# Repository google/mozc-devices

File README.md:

Circuit diagrams and firmware source code for Gboard DIY keyboards, previously
known as Google Japanese Input / Gboard April Fools.

This is not an officially supported Google product.

# Products

Please refer to the README in each directory for more details.

<table>
<tr>
<td>

[Google 日本語入力 ドラムセットバージョン](https://archive.google/drumsetkeyboard/)<br>
[Google Japanese Input Drum set version](https://archive.google/drumsetkeyboard/)

変換の煩わしさを感じさせない思いどおりの日本語入力を提供します。

- [Announce](https://blog.google/intl/ja-jp/products/android-chrome-play/2010_04_google/)
- Release date: Apr 1, 2010
- Source: Not open source

</td>
<td>

[Google 日本語入力 モールスバージョン](http://www.google.co.jp/ime/-.-.html)<br>
[Google Japanese Input Morse version](http://www.google.co.jp/ime/-.-.html)

モールス符号で思いどおりの日本語入力

- [Promotional video](https://www.youtube.com/watch?v=u5AYb778pwA)
- [Announce](https://japan.googleblog.com/2012/04/google.html)
- [Technical details](http://googledevjp.blogspot.jp/2012/06/google.html)
- Release date: Apr 1, 2012
- Source: [/third_party/mozc-morse](./third_party/mozc-morse)

</td>
</tr>
<tr>
<td>

[Google 日本語入力 パタパタバージョン](http://www.google.co.jp/ime/patapata/)<br>
[Google Japanese Input Patapata version](http://www.google.co.jp/ime/patapata/)

もう、なにも覚える必要はありません。
押して離すだけの日本語入力。

- [Promotional video](https://www.youtube.com/watch?v=HzUDAaYMNsA)
- [Announce](https://japan.googleblog.com/2013/04/google-patapata.html)
- [Technical details](http://googledevjp.blogspot.jp/2013/10/google.html)
- Release date: Apr 1, 2013
- Source: [/third_party/mozc-flap](./third_party/mozc-flap)

</td>
<td>

[Google 日本語入力 マジックハンドバージョン](https://archive.google/ime/m9/)<br>
[Google Japanese Input Magic hand version](https://archive.google/ime/m9/)

マジックハンドでらくらく入力

- [Promotional video](https://www.youtube.com/watch?v=0u1zoaJYAmw)
- [Announce](https://blog.google/intl/ja-jp/products/android-chrome-play/2014_04_m9/)
- Release date: Apr 1, 2014
- Source: Not open source

</td>
</tr>
<tr>
<td>

[Google 日本語入力 ピロピロバージョン](https://www.google.co.jp/ime/___o/)<br>
[Google Japanese Input Piropiro version](https://www.google.co.jp/ime/___o/)

もうキーはいらない

- [Promotional video](https://www.youtube.com/watch?v=gAgOnQqyDz0)
- [Announce](https://japan.googleblog.com/2015/04/piropiro.html)
- Release date: Apr 1, 2015
- Source: [/mozc-piropiro](./mozc-piropiro)

</td>
<td>

[Google 日本語入力 物理フリックバージョン](https://www.google.co.jp/ime/furikku/)<br>
[Google Japanese Input Physical Flick version](https://www.google.co.jp/ime/furikku/)

さわれるフリック

- [Promotional video](https://www.youtube.com/watch?v=5LI1PysAlkU)
- [Announce](https://japan.googleblog.com/2016/04/furikku.html)
- Release date: Apr 1, 2016
- Source: [/mozc-furikku](./mozc-furikku)

</td>
</tr>
<tr>
<td>

[日本語入力 プチプチバージョン](https://landing.google.co.jp/ime/ooooo/)<br>
[Google Japanese Input Puchi Puchi version](https://landing.google.co.jp/ime/ooooo/)

空気のように、軽やかな入力。

- [Promotional video](https://www.youtube.com/watch?v=RkJZDvHMyTA)
- [Announce](https://japan.googleblog.com/2017/04/ooooo.html)
- Release date: Apr 1, 2017
- Source: [/third_party/mozc-puchi](./third_party/mozc-puchi)

</td>
<td>

[Gboard 物理手書きバージョン](https://landing.google.co.jp/tegaki/)<br>
[Gboard Physical Handwriting version](https://landing.google.co.jp/tegaki/)

新しいタイプの手書き入力。

- [Promotional video](https://www.youtube.com/watch?v=guJnFY1R4I0)
- [Announce](https://japan.googleblog.com/2018/04/tegaki.html)
- [Technical details](https://developers-jp.googleblog.com/2018/04/tegaki.html)
- Release date: Apr 1, 2018
- Source: [/mozc-nazoru](./mozc-nazoru)

</td>
</tr>
<tr>
<td>

[Gboard スプーン曲げバージョン](https://landing.google.co.jp/---o/)<br>
[Gboard Spoon Bending version](https://landing.google.co.jp/---o/)

タネも仕掛けもない、柔軟な入力。

- [Promotional video](https://www.youtube.com/watch?v=DeJY5d14qKs)
- [Announce](https://japan.googleblog.com/2019/04/mageru.html)
- Release date: Apr 1, 2019
- Source:
  - [/mozc-mageru](./mozc-mageru) for firmware, schematics, and PCB layout.
  - [/third_party/mozc-mageru](./third_party/mozc-mageru) for 3D model.

</td>
<td>

[Gboard 湯呑みバージョン](https://g.co/yunomi/)<br>
[Gboard yunomi version](https://g.co/yunomi/)

もう、おすしかない。

- [Promotional video](https://www.youtube.com/watch?v=20pC05yisRM)
- [Announce](https://japan.googleblog.com/2021/10/gboard.html)
- Release date: Oct 1, 2021
- Source: [/mozc-yunomi](./mozc-yunomi)

</td>
</tr>
<tr>
<td>

[Gboard 棒バージョン](https://g.co/____)<br>
[Gboard bar version](https://g.co/____)

キーの次はボーです。

- [Promotional video](https://www.youtube.com/watch?v=9G3DWHf1xX0)
- [Announce](https://japan.googleblog.com/2022/10/gboard-2022.html)
- Release date: Oct 1, 2022
- Source: [/mozc-bar](./mozc-bar)

</td>
<td>

[Gboard 帽バージョン](https://g.co/CAPS)<br>
[Gboard CAPS version](https://g.co/CAPS)

入力は、帽険だ。

- [Promotional video](https://www.youtube.com/watch?v=6vib77CUxNM)
- [Announce](https://japan.googleblog.com/2023/10/caps.html)
- Release date: Oct 1, 2023
- Source: [/mozc-caps](./mozc-caps)

</td>
</tr>
<tr>
<td>

[Gboard 両面バージョン](https://g.co/double-sided)<br>
[Gboard double sided version](https://g.co/double-sided)

表面かと思ったら裏面でした。

- [Promotional video](https://www.youtube.com/watch?v=EHqPrHTN1dU)
- [Announce](https://blog.google/intl/ja-jp/products/android-chrome-play/gboard-2024)
- Release date: Oct 1, 2024
- Source: [/mozc-doublesided](./mozc-doublesided)

</td>
<td>

[Gboard ダイヤルバージョン](./mozc-dial/README_ja.md)<br>
[Gboard Dial Version](./mozc-dial)

まるくおさめました。

- [Promotional video](https://youtu.be/BgdWyD0cBx4)
- [Announce](https://blog.google/intl/ja-jp/products/android-chrome-play/gboard-2025)
- Release date: Oct 1, 2025
- Source: [/mozc-dial](./mozc-dial)

</td>
</tr>
<tr>
<td>

[Gboard くるくる バージョン](./mozc-conveyorbelt/README_ja.md)<br>
[Gboard Conveyor Belt version](./mozc-conveyorbelt)

流れるような文字入力を

- [Promotional video](https://www.youtube.com/watch?v=DAn34l_YrUM)
- [Announce](https://blog.google/intl/ja-jp/products/android-chrome-play/gboard-2026/)
- Release date: Oct 1, 2026
- Source: [/mozc-conveyorbelt](./mozc-conveyorbelt)

</td>
<td>
</td>
</tr>
</table>

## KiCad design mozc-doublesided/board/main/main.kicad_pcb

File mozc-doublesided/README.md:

# Gboard double sided version

This directory contains the firmware and hardware design for Gboard double sided
version, which was released on **Oct 1, 2024**.

This is not an officially supported Google product.

## Contents

The directory structure is as follows:

-   case/ : STL files for case
-   board/ : KiCad schematics and PCB layouts
-   firmware/ : Firmware resources for STM32CubeIDE
-   gerber/ : Gerber data for PCB production and assembly

## Building Gboard double-sided Version

### Parts

-   Assembled A Type Board: 26 boards (incl. 1 primary board) - See BOM below
-   Assembled B Type Board: 26 boards (incl. 1 primary board) - See BOM below
-   USB Board: 1 board - See BOM below
-   Cable A; JST ZH 1.5mm pitch 8pin 100mm forward double head: 25 units
-   Cable B; JST ZH 1.5mm pitch 7pin 100mm forward double head: 1 units
-   Pin Header; 1x4 pin 2.54mm pitch 12+mm height,
    ([sample](https://akizukidenshi.com/catalog/g/g101382/)): 52 headers.
-   3D printed case: 26 pcs
-   Self tapping screw (M2 10mm): 52 pcs
-   Key switch (Cherry MX or compatible): 208 pcs.
-   Key caps (For Cherry MX switch): 208 pcs.

#### A Type Board BOM

| Reference | Description                         | Qty | Note               |
| --------- | ----------------------------------- | --- | ------------------ |
| R1-R2     | 0402(metric: 1005) Resistor 510 ohm | 2   |                    |
| R3-R4     | 0603(metric: 1608) Resistor 1K ohm  | 2   | Primary board only |
| J2-J3     | JST S8B-ZR                          | 2   |                    |
| J4        | JST S7B-ZR                          | 1   | Primary board only |
| U1        | STMicro STM32F042F4P6               | 1   |                    |
| SW1-SW4   | Kailh CPG151101S11-1                | 4   |                    |
| D1-D4     | OPSCO Optoelectronics SK6812MINI-E  | 4   |                    |
| D5-D8     | 0805(metric: 2012) Small Signal Switching Diode | 4   |        |
| C1        | 0402(metric: 1005) Capacitor 0.1uF  | 1   |                    |

The parts that are only on the primary board are not included in the BOM file
(in `gerber/` directory), so make sure that you choose one board to be the
primary board and solder in the primary board specific parts.

#### B Type Board BOM

Reference | Description                                     | Qty | Note
--------- | ----------------------------------------------- | --- | ----
R2        | 0402(metric: 1005) Resistor 510 ohm             | 1   |
SW1-SW4   | Kailh CPG151101S11-1                            | 4   |
D1-D4     | OPSCO Optoelectronics SK6812MINI-E              | 4   |
D5-D8     | 0805(metric: 2012) Small Signal Switching Diode | 4   |

#### USB Board BOM

Reference | Description                          | Qty | Note
--------- | ------------------------------------ | --- | ----
U1        | 1A/3.3V Regulator AMS1117-3.3        | 1   |
R1-R2     | 0402(metric: 1005) Resistor 5.1K ohm | 2   |
R3-R4     | 0402(metric: 1005) Resistor 22 ohm   | 2   |
R5        | 0402(metric: 1005) Resistor 1.5K ohm | 1   |
J1        | JST S7B-ZR                           | 1   |
J2        | USB Type-C 16pin connector           | 1   |
C1        | 0402(metric: 1005) Capacitor 10uF    | 1   |
C2        | 0402(metric: 1005) Capacitor 2.2uF   | 1   |
C3-C4     | 0402(metric: 1005) Capacitor 47pF    | 2   |

### Hardware

#### Step 1: Prepare 3d printed parts

The `case/` directory of this repository has STL files for the case. The case
consists of 26 parts (case00.stl - case25.stl). Each part has a number engraved
on the inside. For example, when assembling, you will insert the protrusion of
case 0 into the hole of case 1.

We also provide a jig (`case/jig.stl`) for soldering between the A type boards
and B type boards. Please print this too.

#### Step 2: Prepare PCB

**PCB Production and Assembly**

First, you need to build 26 A type boards and 26 B type boards, and one USB
board. You may be able to use existing gerber data, BOM, and CPL (positions)
from `gerber/` directory.

Board Type | Gerber         | BOM                | CPL
---------- | -------------- | ------------------ | ------------------------
A          | main_panel.zip | main_panel_bom.csv | main_panel_positions.csv
B          | sub_panel.zip  | sub_panel_bom.csv  | sub_panel_positions.csv
USB        | usb.zip        | usb_bom.csv        | usb_positions.csv

Prepared board data for the A type board and the B type board contains 9 boards
in a panel. So, you need to produce 3 panels to build 27 (26 required + 1 spare)
boards. You also need one USB board.

**Firmware upload**

Next, let's burn the prebuilt firmware.

Connect the following 4 pads, SWDIO, SWCLK, GND, and +3.3V with ST-LINK. You can
use
[STM32CubeProgrammer](https://www.st.com/ja/development-tools/stm32cubeprog.html)
to configure the device and to burn the prebuilt firmware. There's no connector,
just holes in the PCB so make sure you keep a secure connection while
programming the device.

Once the programmer establishes the connection with the A type board, you need
to write the `Option bytes`. Under the `User Configuration` section, you will
see the `BOOT_SEL` bit. You need to ensure the bit is unchecked before pushing
the `Apply` button.

Next, you will go to the `Erasing & Programming` section to burn the prebuilt
firmware, `firmware/prebuilt/mozc.elf`. Select the binary from the `Browse`
button, put `0x08000000` for the `Start address`, then press the `Start
Programming` button.

You need to burn the same settings and firmware into all the Boards A.

**Primary A Type Board Specific Modifications**

You need to choose one of the A type boards to be the primary A type board and
add three parts to it.

1.  J4 JST S7B-ZR connector header
2.  R3 0603 Resistor 1K ohm
3.  R4 0603 Resistor 1K ohm

**Construct the A/B Type Board Pair Modules**

You need to prepare 26 pairs of the A type board and B type board. They should
be paired as the following picture shows. Each `P Connector` and each `S
connector` should be connected using the 1x4 pin headers respectively.

Make sure that the `IN` side of the A type board and B type board face each
other.

Also, the distance should be adjusted to fit the case. It will help to print the
included jig STL to hold both boards while soldering the pin headers.

#### Step 3: Insert PCB to case

**Primary A/B Pair Module**

Connect the primary module and the USB board.

Insert the USB board into case 0.

**All Pair Modules**

Insert each paired module into a case. You need to ensure the A type board is
always placed on the bottom side.

#### Step 4: Connect the cases together

You need to connect all the `UP` socket and `DOWN` socket pairs. Please be
careful not to connect the same type of socket, i.e. `UP` and `UP`, or `DOWN`
and `DOWN` together. It will cause a short circuit and destroy the chips when
powered on. If you notice a smell or see smoke, disconnect the power
immediately. This may prevent damage to the boards.

The below picture shows the connections. Please make sure that module 0 and
module 25 are not connected to each other.

Note that this picture is simplified and doesn't reflect the 3d structure of the
keyboard. So, module 25 will be placed upside down.

You can use screws to keep the boards tightly connected.

### Firmware

#### Step 1: Environment setup

You need to install STMicroelectronics's official tools to develop STM32.

-   [STM32CubeIDE](https://www.st.com/en/development-tools/stm32cubeide.html) -
    Confirmed with 1.16.1.
-   [STM32CubeMX](https://www.st.com/en/development-tools/stm32cubemx.html) -
    Confirmed with 6.12.1.

Alternatively, you can use Visual Studio Code with the STM32 VS Code Extension,
STM32CubeMX, and STM32CubeCLT if your development environment is not on Windows.

-   [Visual Studio Code](https://code.visualstudio.com/) - Confirmed with
    1.93.0.
-   [STM32 VS Code Extension](https://marketplace.visualstudio.com/items?itemName=stmicroelectronics.stm32-vscode-extension) -
    Confirmed with 2.1.0.
-   [STM32CubeCLT](https://www.st.com/en/development-tools/stm32cubeclt.html) -
    Confirmed with 1.16.1. You will be asked to specify the path to the VS Code
    Extension. You may add `{ "STM32VSCodeExtension.cubeCLT.path":
    "/opt/ST/STM32CubeCLT_1.16.1" }` to `.vscode/settings.json`.

    You will need the
    [ST-LINK](https://www.st.com/ja/development-tools/st-link-v2.html) or
    something equivalent to upload the firmware.

#### Step 2: Compile and upload

**Steps for the STM32CubeIDE:**

1.  Launch STM32CubeIDE with `mozc-doublesided` directory as `workspace`.
2.  Start a project via `Start new project from STM32CubeMX file (.ioc)` to open
    a configuration dialog.
3.  Select `firmware/mozc-doublesided.ioc` as `STM32CubeMX .ioc file` and push
    `Finish` button to generated required resources.
4.  Apply patches. (See the following instructions)
5.  Set `Release` as the active project, from `Project > Build Configurations >
    Set Active > 2 Release`. `Debug` doesn't fit the available memory size.
6.  Build, from `Project > Build All`.

The built binary will be produced at `firmware/Release/firmware.elf`.

**Steps for the Visual Studio Code:**

1.  Open `firmware/mozc-doublesided.ioc` by STM32CubeMX and push the `GENERATE
    CODE` button. You may need to follow instructions if you are asked to
    install something required in the process.
2.  Launch VSCode and open the folder `firmware`.
3.  Apply patches. (See the following instructions)
4.  Select `Release` or `RelWithDebInfo` from the build presets. `Debug` doesn't
    fit the available memory size.
5.  `Build` from the status bar, or other user interfaces.

The built binary will be produced at `build/Release/firmware.elf`.

If you saw errors on linking the binary involving `STM32F042F6Px_FLASH.ld`, you
may need a patch to make it work with your installed toolchain.

Try `patch < STM32F042F6Px_FLASH.ld.diff`.

**Steps to apply patches:**

In the `firmware` directory, apply the `firmware.diff` patch to the generate
resources via the following command.

`$ patch -p1 < firmware.diff`

## License

See [LICENSE](../LICENSE) file in this directory.

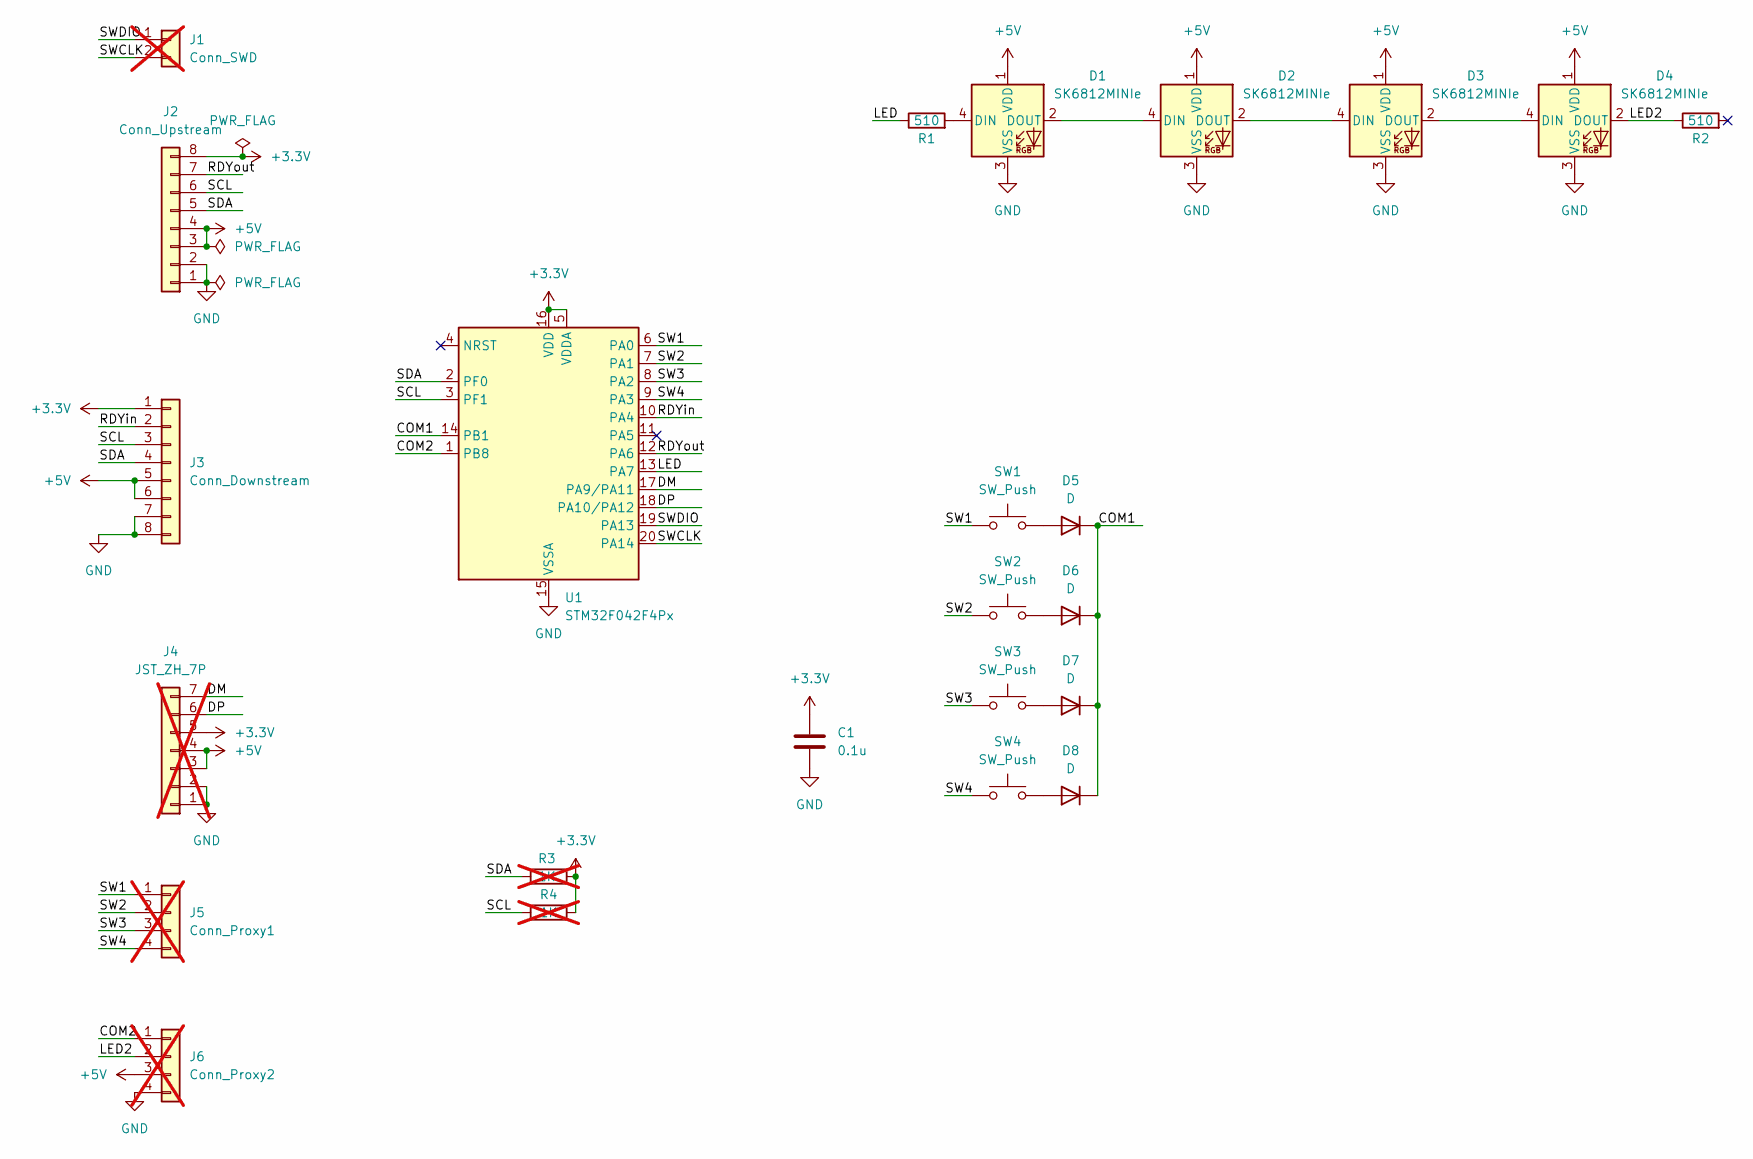
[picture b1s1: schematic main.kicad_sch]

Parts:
C1: 0.1u; C_0402_1005Metric
D1, D2, D3, D4: SK6812MINIe; SK6812MINIe (Reverse); MPN C5149201
D5, D6, D7, D8: D; D_0805_2012Metric; MPN C109001
J1: Conn_SWD; PinHeader_1x02_P2.54mm_Vertical; not fitted
J2: Conn_Upstream; JST_S8B_ZR; MPN C2845571
J3: Conn_Downstream; JST_S8B_ZR; MPN C2845571
J4: JST_ZH_7P; JST_S7B_ZR; MPN C160734; not fitted
J5: Conn_Proxy1; PinHeader_1x04_P2.54mm_Vertical; not fitted
J6: Conn_Proxy2; PinHeader_1x04_P2.54mm_Vertical; not fitted
R1, R2: 510; R_0402_1005Metric
R3, R4: 1K; R_0603_1608Metric_Pad0.98x0.95mm_HandSolder; not fitted
SW1, SW2, SW3, SW4: SW_Push; Keyswitch; MPN C5184526
U1: STM32F042F4Px; TSSOP-20_4.4x6.5mm_P0.65mm; MPN C81002

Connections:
+3.3V: C1.1, J2.8, J3.1, J4.5, R3.2, R4.2, U1.5 (VDDA), U1.16 (VDD)
+5V: D1.1 (VDD), D2.1 (VDD), D3.1 (VDD), D4.1 (VDD), J2.3, J2.4, J3.5, J3.6, J4.3, J4.4, J6.3
/COM1: D5.1 (K), D6.1 (K), D7.1 (K), D8.1 (K), U1.14 (PB1)
/COM2: J6.1, U1.1 (PB8)
/DM: J4.7, U1.17 (PA9/PA11)
/DP: J4.6, U1.18 (PA10/PA12)
/LED: R1.1, U1.13 (PA7)
/LED2: D4.2 (DOUT), J6.2, R2.1
/RDYin: J3.2, U1.10 (PA4)
/RDYout: J2.7, U1.12 (PA6)
/SCL: J2.6, J3.3, R4.1, U1.3 (PF1)
/SDA: J2.5, J3.4, R3.1, U1.2 (PF0)
/SW1: J5.1, SW1.1, U1.6 (PA0)
/SW2: J5.2, SW2.1, U1.7 (PA1)
/SW3: J5.3, SW3.1, U1.8 (PA2)
/SW4: J5.4, SW4.1, U1.9 (PA3)
/SWCLK: J1.2, U1.20 (PA14)
/SWDIO: J1.1, U1.19 (PA13)
GND: C1.2, D1.3 (VSS), D2.3 (VSS), D3.3 (VSS), D4.3 (VSS), J2.1, J2.2, J3.7, J3.8, J4.1, J4.2, J6.4, U1.15 (VSSA)
unnamed: D1.4 (DIN), R1.2
unnamed: D1.2 (DOUT), D2.4 (DIN)
unnamed: D2.2 (DOUT), D3.4 (DIN)
unnamed: D3.2 (DOUT), D4.4 (DIN)
unnamed: D5.2 (A), SW1.2
unnamed: D6.2 (A), SW2.2
unnamed: D7.2 (A), SW3.2
unnamed: D8.2 (A), SW4.2

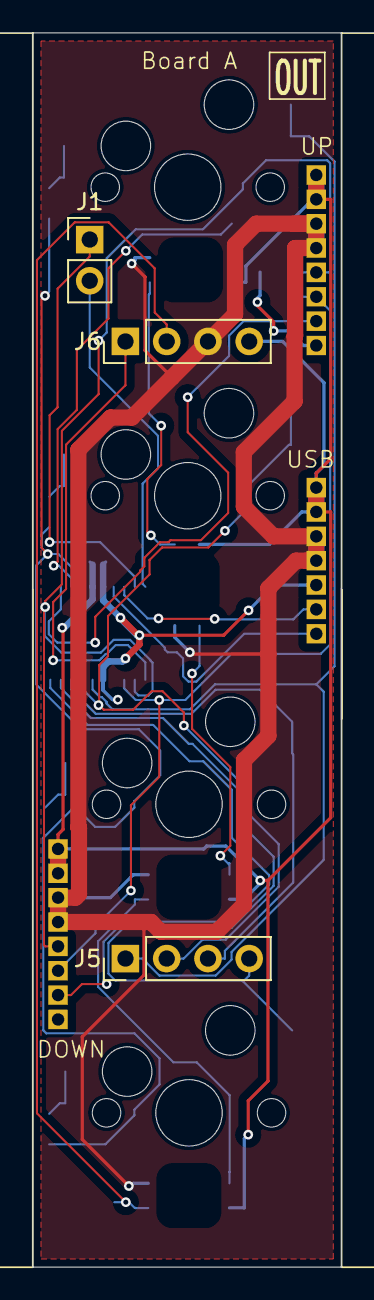
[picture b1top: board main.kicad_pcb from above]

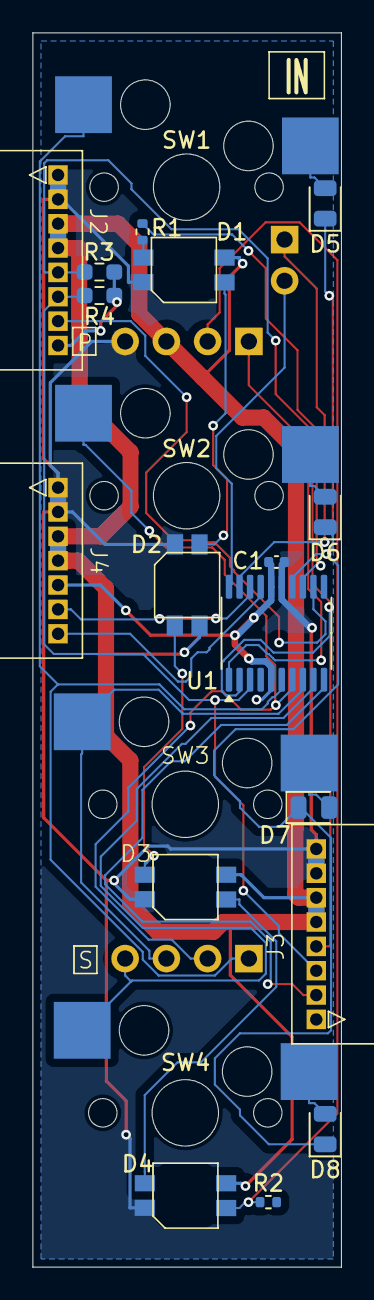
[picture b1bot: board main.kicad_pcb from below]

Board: 4 copper layers, 19.0 x 76.0 mm, 26 parts (21 on the bottom side), 27 nets.

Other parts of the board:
CUT1, CUT2: CUT

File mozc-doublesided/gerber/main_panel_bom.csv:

Designator,Footprint,Quantity,Value,LCSC Part #
"C1_9, C1_8, C1_7, C1_6, C1_5, C1_4, C1_3, C1_2, C1",0402,9,0.1u,
"CUT1_9, CUT1_8, CUT1_7, CUT1_6, CUT1_5, CUT1_4, CUT1_3, CUT1_2, CUT1, CUT2_9, CUT2_8, CUT2_7, CUT2_6, CUT2_5, CUT2_4, CUT2_3, CUT2_2, CUT2",CUT,18,CUT,
"D1_9, D1_8, D1_7, D1_6, D1_5, D1_4, D1_3, D1_2, D1, D2_9, D2_8, D2_7, D2_6, D2_5, D2_4, D2_3, D2_2, D2, D3_9, D3_8, D3_7, D3_6, D3_5, D3_4, D3_3, D3_2, D3, D4_9, D4_8, D4_7, D4_6, D4_5, D4_4, D4_3, D4_2, D4",SK6812MINIe (Reverse),36,SK6812MINIe,C5149201
"D5_9, D5_8, D5_7, D5_6, D5_5, D5_4, D5_3, D5_2, D5, D6_9, D6_8, D6_7, D6_6, D6_5, D6_4, D6_3, D6_2, D6, D7_9, D7_8, D7_7, D7_6, D7_5, D7_4, D7_3, D7_2, D7, D8_9, D8_8, D8_7, D8_6, D8_5, D8_4, D8_3, D8_2, D8",0805,36,D,C109001
"J2_9, J2_8, J2_7, J2_6, J2_5, J2_4, J2_3, J2_2, J2",JST_S8B_ZR,9,Conn_Upstream,C2845571
"J3_9, J3_8, J3_7, J3_6, J3_5, J3_4, J3_3, J3_2, J3",JST_S8B_ZR,9,Conn_Downstream,C2845571
"R1_9, R1_8, R1_7, R1_6, R1_5, R1_4, R1_3, R1_2, R1, R2_9, R2_8, R2_7, R2_6, R2_5, R2_4, R2_3, R2_2, R2",0402,18,510,
"SW1_9, SW1_8, SW1_7, SW1_6, SW1_5, SW1_4, SW1_3, SW1_2, SW1, SW2_9, SW2_8, SW2_7, SW2_6, SW2_5, SW2_4, SW2_3, SW2_2, SW2, SW3_9, SW3_8, SW3_7, SW3_6, SW3_5, SW3_4, SW3_3, SW3_2, SW3, SW4_9, SW4_8, SW4_7, SW4_6, SW4_5, SW4_4, SW4_3, SW4_2, SW4",Keyswitch,36,SW_Push,C5184526
"U1_9, U1_8, U1_7, U1_6, U1_5, U1_4, U1_3, U1_2, U1",TSSOP-20_4.4x6.5mm_P0.65mm,9,STM32F042F4Px,C81002

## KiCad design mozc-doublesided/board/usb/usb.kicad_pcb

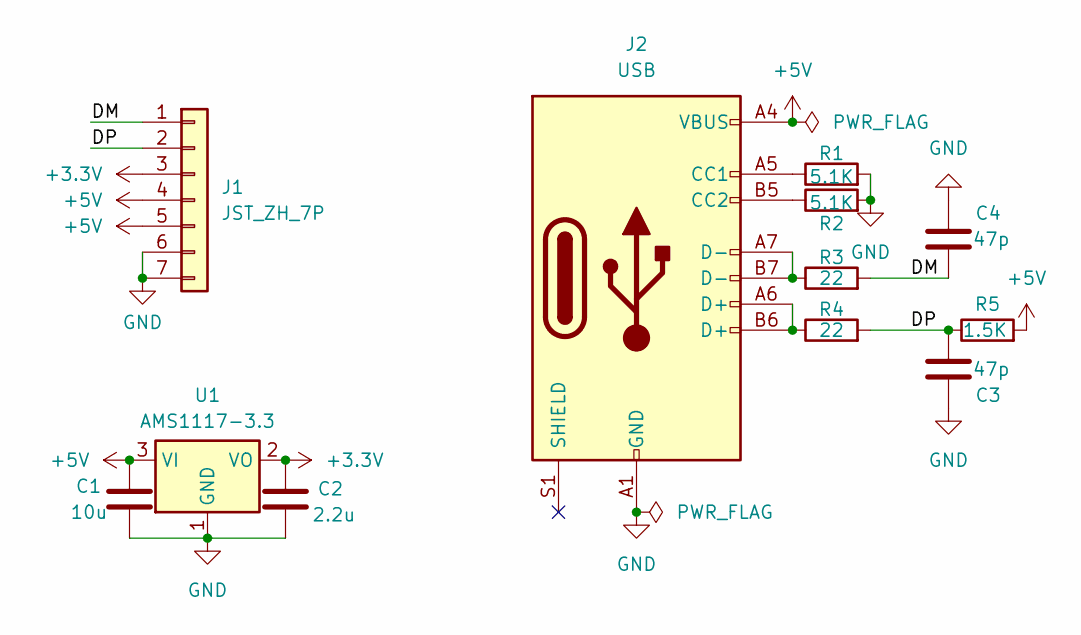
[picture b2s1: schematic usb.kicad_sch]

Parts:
C1: 10u; C_0402_1005Metric
C2: 2.2u; C_0402_1005Metric
C3, C4: 47p; C_0402_1005Metric
J1: JST_ZH_7P; JST_S7B_ZR; MPN C160734
J2: USB; USB_C_Receptacle_XKB_U262-16XN-4BVC11; MPN C5178539
R1, R2: 5.1K; R_0402_1005Metric
R3, R4: 22; R_0402_1005Metric
R5: 1.5K; R_0402_1005Metric
U1: AMS1117-3.3; SOT-223-3_TabPin2; MPN C347222

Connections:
+3.3V: C2.2, J1.3, U1.2 (VO)
+5V: C1.2, J1.4, J1.5, J2.A4 (VBUS), J2.A9 (VBUS), J2.B4 (VBUS), J2.B9 (VBUS), R5.2, U1.3 (VI)
/DM: C4.2, J1.1, R3.2
/DP: C3.1, J1.2, R4.2, R5.1
GND: C1.1, C2.1, C3.2, C4.1, J1.6, J1.7, J2.A1 (GND), J2.A12 (GND), J2.B1 (GND), J2.B12 (GND), R1.2, R2.2, U1.1 (GND)
unnamed: J2.A5 (CC1), R1.1
unnamed: J2.B5 (CC2), R2.1
unnamed: J2.A6 (D+), J2.B6 (D+), R4.1
unnamed: J2.A7 (D-), J2.B7 (D-), R3.1

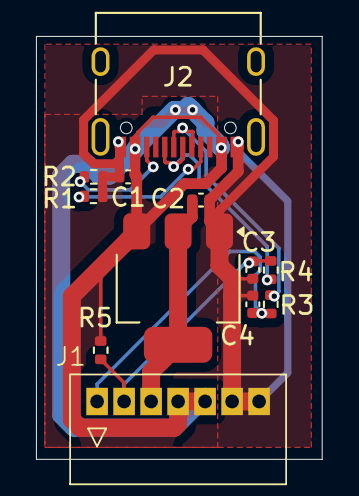
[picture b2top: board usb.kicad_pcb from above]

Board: 2 copper layers, 15.9 x 23.5 mm, 12 parts (0 on the bottom side), 9 nets.

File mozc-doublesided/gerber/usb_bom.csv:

Designator,Footprint,Quantity,Value,LCSC Part #
C1,0402,1,10u,
C2,0402,1,2.2u,
"C3, C4",0402,2,47p,
J1,JST_S7B_ZR,1,JST_ZH_7P,C160734
J2,USB_C_Receptacle_XKB_U262-16XN-4BVC11,1,USB,
"R1, R2",0402,2,5.1K,
"R3, R4",0402,2,22,
R5,0402,1,1.5K,
U1,SOT-223-3_TabPin2,1,AMS1117-3.3,C347222

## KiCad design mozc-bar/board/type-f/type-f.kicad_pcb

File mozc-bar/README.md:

# Gboard Bar version

This directory contains programs, schematics and board layouts for Gboard Bar version,
which was released on **Oct 1, 2022**.

This is not an officially supported Google product.

## Contents

The directory structure is as follows:

- board/ : KiCad schematics and PCB layouts.
- case/ : STL file for case.
- firmware/ : Arduino sketch.

## Building Gboard Bar Version

### Parts

- [Cherry MX (or compatible) key](https://shop.yushakobo.jp/collections/all-switches/cherry-mx-%E4%BA%92%E6%8F%9B-%E3%82%B9%E3%82%A4%E3%83%83%E3%83%81) x 101
- [Stabilizer](https://shop.yushakobo.jp/collections/all-keyboard-parts/products/a0500st?variant=37665699463329) 2u x 7
- [Stabilizer](https://shop.yushakobo.jp/collections/all-keyboard-parts/products/a0500st?variant=37665699463329) 6.25u x 1
- [74HC165](https://akizukidenshi.com/catalog/g/gI-14679/) x 16
- [Resistor 100kOhm](https://akizukidenshi.com/catalog/g/gR-25104/) x 16
- [Resistor network 100kOhm](https://akizukidenshi.com/catalog/g/gR-14228/) x 16
- [Capacitor 0.1uF](https://akizukidenshi.com/catalog/g/gP-10147/) x 16
- 2 row 3 column right angle 2.54mm pin headers x 16 ([Cut from this](https://akizukidenshi.com/catalog/g/gC-10903/))
- 2 row 3 column right angle 2.54mm pin header sockets x 16 ([Cut from this](https://akizukidenshi.com/catalog/g/gC-05756/))
- 20 mm width x 10 mm height extruded aluminium frame 2313.75mm in length (needed length may vary slightly based on 3D printing size variance)
- [M3 6mm slim head screw](https://jp.misumi-ec.com/vona2/detail/221000546066) x 16
- [M3 5mm Spacer](https://akizukidenshi.com/catalog/g/gP-07471/) x 16
- [M3 nut](https://akizukidenshi.com/catalog/g/gP-07468/) x 16
- Keycap (US) x 1set
- If building the wired version.
  - ProMicro x 1
  - Pin header 12pin x 2
- If building the wireless version.
  - M5StickC (or M5StickC PLUS) x 1
  - Right angle pin header 8pin x 1

#### Aluminium Frame

These for making frame:

- [HFSFIN5-1020](https://jp.misumi-ec.com/vona2/detail/110302374340/)
  - Multiple extruded aluminium frames can be connected together using [straight line connectors](https://jp.misumi-ec.com/vona2/detail/110302248430). For example, you may choose to order three 0.8m-ish frames instead of a single 2.4m frame.
  - However, the bottom holes of the cases cannot be used for fastening them to the frame. Additional machining would be needed. (e.g. dig some hole to the frame, or use glue instead, etc.)
- [AFS-1020-4](https://jp.misumi-ec.com/vona2/detail/221005476984/)
  - [NHG-04-3 square nuts](https://jp.misumi-ec.com/vona2/detail/221005480709/) and M3 flat-headed screws can be used for fastening each module to the frame.
  - However, parts for connecting these frames are not available. Purchasing a 2.4m-length frame may be problematic.
  - We have not actually tried this yet.

### PCBs

We need the following quantities of each kind of PCB:

- Controller x 1
- Key switch Type A x 8
- Key switch Type B x 3
- Key switch Type C x 1
- Key switch Type D x 1
- Key switch Type E x 1
- Key switch Type F x 1
- Key switch Type G x 1

### Case

The following quantities of each type of 3D print case:

- case/left-tip.stl x 1
- case/typeA.stl x 8
- case/typeB.stl x 3
- case/typeC.stl x 1
- case/typeD.stl x 1
- case/typeE.stl x 1
- case/typeF.stl x 1
- case/typeG.stl x 1
- case/controller.stl x 1
- case/right-tip.stl x 1

### Steps to build

#### Step 1

Solder 74HC165, resistors, resistor networks, capacitors, connectors and keyswitches to keyswitch PCBs.

#### Step 2

Add stabilizer and keycaps.

Here is the default keymap:

#### Step 3

Solder pin header and/or pro micro to controller PCB.

Wired version (Use ProMicro):

Wireless version (Use M5StickC):

#### Step 4

Attach each PCB to 3D printed case using M3 bolt and spacer.

#### Step 5

Thread the aluminium frame through the square holes of the 3D printed cases to join them together.

#### Step 6

Install firmware using the Arduino IDE.

NOTE: For the wireless version (M5Stack), an additional library is needed:
[ESP32 BLE Keyboard library](https://github.com/T-vK/ESP32-BLE-Keyboard)

#### Step 7

Connect the keyboard to a PC or other device that has Google Japanese
Input/Gboard installed.

## License

```
Licensed under the Apache License, Version 2.0 (the "License"); you may
not use this file except in compliance with the License. You may obtain
a copy of the License at

    http://www.apache.org/licenses/LICENSE-2.0

Unless required by applicable law or agreed to in writing, software
distributed under the License is distributed on an "AS IS" BASIS,
WITHOUT WARRANTIES OR CONDITIONS OF ANY KIND, either express or implied.
See the License for the specific language governing permissions and
limitations under the License.
```

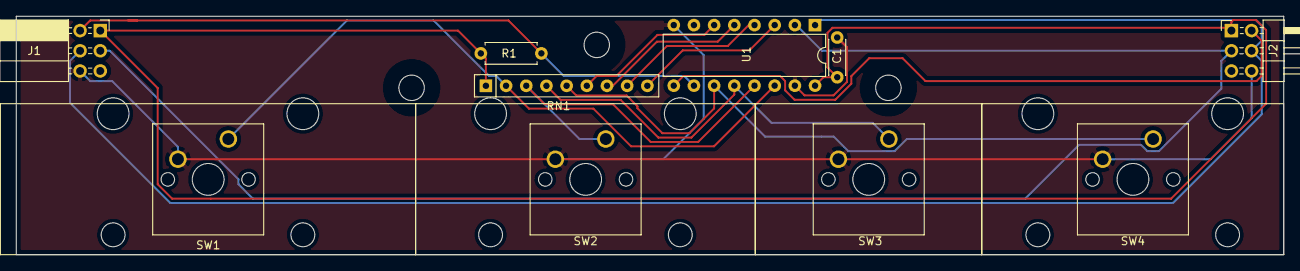
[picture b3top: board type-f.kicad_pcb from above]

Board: 2 copper layers, 159.5 x 30.0 mm, 25 parts (0 on the bottom side), 14 nets.

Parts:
C1: C; C_Disc_D4.3mm_W1.9mm_P5.00mm
H1, H101, H102: MountingHole; MountingHole_3.2mm_M3
H2, H4, H6, H8, H10, H12: MountingHole; 4mm
H3, H5, H7, H9, H11, H13: MountingHole; 3mm
J1: Conn_01x06_Female; PinSocket_2x03_P2.54mm_Horizontal
J2: Conn_01x06_Male; PinHeader_2x03_P2.54mm_Horizontal
R1: 100k; R_Axial_DIN0207_L6.3mm_D2.5mm_P7.62mm_Horizontal
RN1: 100k; R_Array_SIP9
SW1, SW2, SW3, SW4: SW_Push; SW_Cherry_MX_1.00u_PCB
U1: 74HC165; DIP-16_W7.62mm

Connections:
/CLK_IN: J1.3, J2.3, U1.2
/DATA_IN: J1.2, R1.1, U1.10
/DATA_OUT: J2.2, U1.9
/LOAD_IN: J1.4, J2.4, U1.1
GND: C1.2, J1.6, J2.6, SW1.2, SW2.2, SW3.2, SW4.2, U1.8, U1.15
SW1: RN1.5, SW4.1, U1.11
SW2: RN1.4, SW3.1, U1.12
SW3: RN1.3, SW2.1, U1.13
SW4: RN1.2, SW1.1, U1.14
SW5: RN1.9, U1.3
SW6: RN1.8, U1.4
SW7: RN1.7, U1.5
SW8: RN1.6, U1.6
VCC: C1.1, J1.1, J2.1, R1.2, RN1.1, U1.16

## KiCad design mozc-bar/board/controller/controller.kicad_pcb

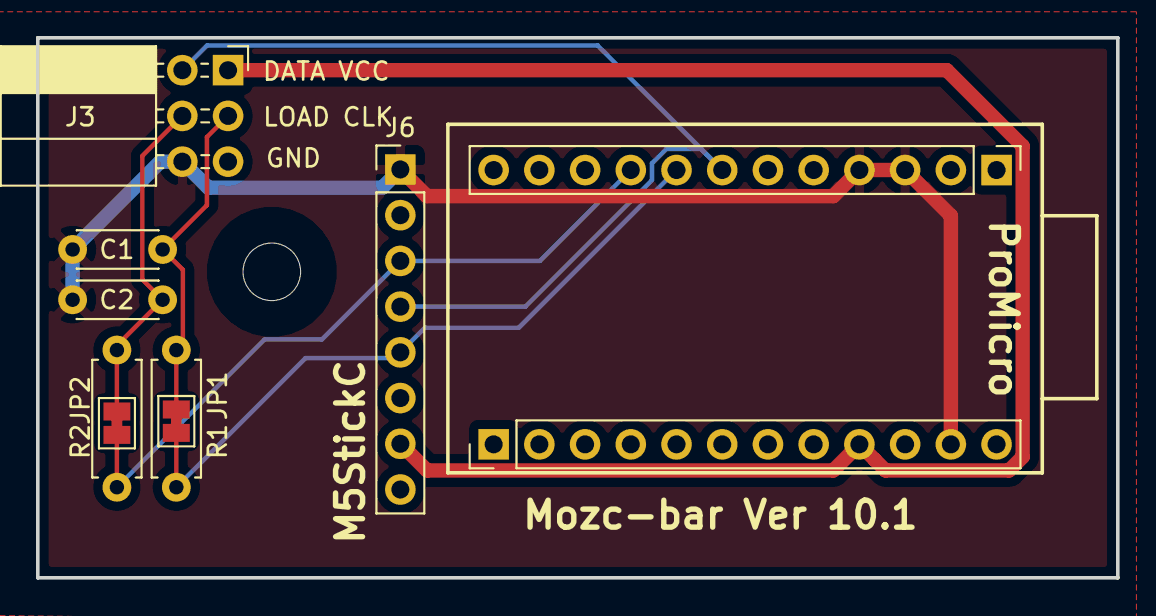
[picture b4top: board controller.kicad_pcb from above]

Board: 2 copper layers, 60.0 x 30.0 mm, 10 parts (0 on the bottom side), 7 nets.

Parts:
C1, C2: C; C_Disc_D4.3mm_W1.9mm_P5.00mm
J1, J2: Conn_01x12_Female; PinHeader_1x12_P2.54mm_Vertical
J3: Conn_01x06; PinSocket_2x03_P2.54mm_Horizontal
J6: Conn_01x08_Male; PinHeader_1x08_P2.54mm_Vertical
JP1, JP2: Jumper; SolderJumper-2_P1.3mm_Bridged_Pad1.0x1.5mm
R1, R2: R; R_Axial_DIN0207_L6.3mm_D2.5mm_P7.62mm_Horizontal

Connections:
/CLK_OUT: J1.8, J6.5, JP1.2, R1.1
/CLK_OUT_BUF: C1.1, J3.3, JP1.1, R1.2
/DATA_IN: J1.7, J3.2, J6.4
/LOAD_OUT: J1.9, J6.3, JP2.2, R2.1
/LOAD_OUT_BUF: C2.1, J3.4, JP2.1, R2.2
GND: C1.2, C2.2, J1.3, J1.4, J2.11, J3.6, J6.1
VCC: J2.9, J3.1, J6.7

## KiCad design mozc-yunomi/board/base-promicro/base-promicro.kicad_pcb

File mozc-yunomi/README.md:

# Gboard Yunomi version

This contains programs, schematics and board layouts for Gboard Yunomi version,
which was released on **Oct 1, 2021**.

This is not an officially supported Google product.

## Contents

The directory structure is as follows:

-   firmware/ : Arduino sketch.
-   board/ : KiCad schematics and PCB layouts.
-   jig.stl : A jig for building the keyboards.
-   ../third_party/mozc-yunomi/keyswitches.pretty : Footprint data for the key
    switches.

## Building Gboard Yunomi Version

**We also have the Pro Micro version of the device, which is easier to build. Please refer to [the Pro Micro README](./README_promicro.md) if you want to build one with Pro Micro.**

### Parts

-   Kailh choc key x60
-   Diode (1N4148) x60
-   ATMega32U4-AU (QFP)
-   Resistor 10kOhm
-   Resistor 22Ohm x2
-   Capacitor 0.1uF
-   Capacitor 1uF x2
-   Capacitor 22pF x2
-   Crystal 16MHz (HC-49)
-   USB-C connector breakout (4pin)

### PCBs

We need two types of PCBs to build this project.

#### Key-PCB

File location: board/key

Shape: Rectangular.

Components: Diodes and key switches.

Number of PCBs required: 12

#### Base-PCB:

File location: board/base

Shape: Dodecagonal

Component2: ATMega32u4.

### Steps to build

#### Step 1

Solder diodes D1 to D5 onto the twelve Key-PCBs at the silk-screened locations.

*IMPORTANT:* Diodes on six of the Key-PCB should be placed in the opposite
direction.

For six of the PCBs, we can solder diodes as indicated by the silk-screen. For
the other six PCBs, we need to solder the diodes in the opposite direction.

#### Step 2

Solder key-switches to each Key-PCB. Note that the diodes need to be placed on
the opposite side of the Key-PCB to the key-switches, as shown by the
silk-screen.

#### Step 3

Create a cylindrical shape by combining the 12 Key-PCBs.

There are six connection points between each pair of Key-PCBs. Connect adjacent
pairs of boards by soldering the tin-plated wires (see the picture).

However, only connect J11 and J12 between the first and last Key-PCB, instead of
all six locations.

If you have a 3D printer, you may print and use jig.stl to help with this step.

#### Step 4

Solder all parts for Base-PCB.

#### Step 5

Connect Base-PCB to the cylinder made in Step 3.

#### Step 6

Install the
[Arduino caterina bootloader](https://github.com/arduino/ArduinoCore-avr/blob/master/bootloaders/caterina/Caterina-Leonardo.hex)
using AVRISP or other ISP tool.

#### Step 7

Install firmware using the Arduino IDE.

#### Step 8

Connect the keyboard to a PC or other device that has Google Japanese
Input/Gboard installed.

## License

```
Licensed under the Apache License, Version 2.0 (the "License"); you may
not use this file except in compliance with the License. You may obtain
a copy of the License at

    http://www.apache.org/licenses/LICENSE-2.0

Unless required by applicable law or agreed to in writing, software
distributed under the License is distributed on an "AS IS" BASIS,
WITHOUT WARRANTIES OR CONDITIONS OF ANY KIND, either express or implied.
See the License for the specific language governing permissions and
limitations under the License.
```

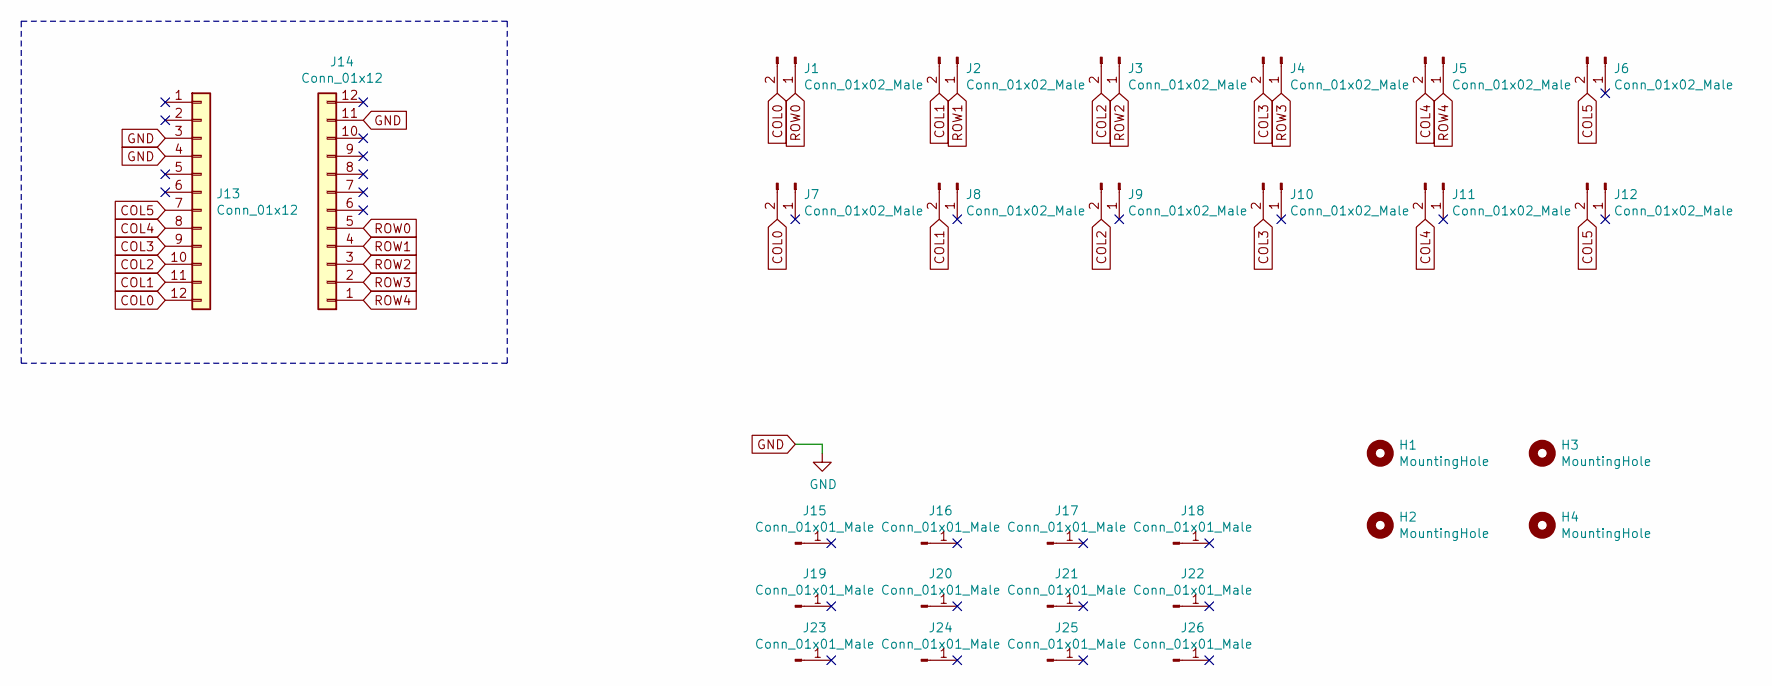
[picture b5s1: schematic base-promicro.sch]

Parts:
H1, H2, H3, H4: MountingHole; MountingHole_2.2mm_M2
J1, J2, J3, J4, J5, J6, J7, J8, J9, J10, J11, J12: Conn_01x02_Male; PinHeader_1x02_P2.54mm_Vertical
J13, J14: Conn_01x12; PinHeader_1x12_P2.54mm_Vertical
J15, J16, J17, J18, J19, J20, J21, J22, J23, J24, J25, J26: Conn_01x01_Male; PinHeader_1x01_P2.54mm_Vertical

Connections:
COL0: J1.2, J7.2, J13.12
COL1: J2.2, J8.2, J13.11
COL2: J3.2, J9.2, J13.10
COL3: J4.2, J10.2, J13.9
COL4: J5.2, J11.2, J13.8
COL5: J6.2, J12.2, J13.7
GND: J13.3, J13.4, J14.11
ROW0: J1.1, J14.5
ROW1: J2.1, J14.4
ROW2: J3.1, J14.3
ROW3: J4.1, J14.2
ROW4: J5.1, J14.1

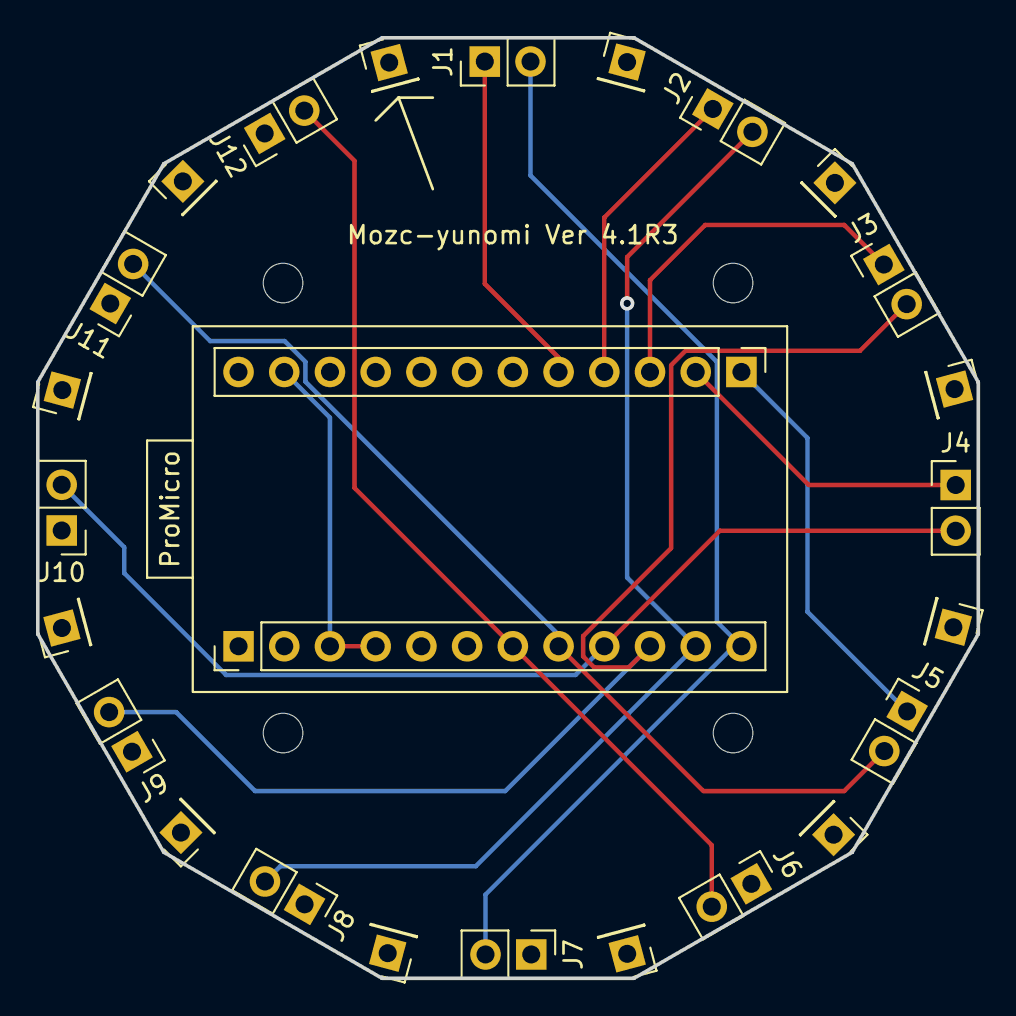
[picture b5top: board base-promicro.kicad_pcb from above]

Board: 2 copper layers, 52.2 x 52.2 mm, 30 parts (0 on the bottom side), 12 nets.

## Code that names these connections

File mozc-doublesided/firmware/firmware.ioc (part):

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Mcu.Name=STM32F042F6Px
Mcu.Package=TSSOP20
Mcu.UserName=STM32F042F6Px
PA0.GPIOParameters=GPIO_PuPd,GPIO_Label
PA0.GPIO_Label=SW1
PA0.GPIO_PuPd=GPIO_PULLUP
PA0.Signal=GPIO_Input
PA1.GPIOParameters=GPIO_PuPd,GPIO_Label
PA1.GPIO_Label=SW2
PA1.GPIO_PuPd=GPIO_PULLUP
PA1.Signal=GPIO_Input
PA11.Mode=Device
PA11.Signal=USB_DM
PA12.Mode=Device
PA12.Signal=USB_DP
PA13.Mode=Serial_Wire
PA13.Signal=SYS_SWDIO
PA14.Mode=Serial_Wire
PA14.Signal=SYS_SWCLK
PA2.GPIOParameters=GPIO_PuPd,GPIO_Label
PA2.GPIO_Label=SW3
PA2.GPIO_PuPd=GPIO_PULLUP
PA2.Signal=GPIO_Input
PA3.GPIOParameters=GPIO_PuPd,GPIO_Label
PA3.GPIO_Label=SW4
PA3.GPIO_PuPd=GPIO_PULLUP
PA3.Signal=GPIO_Input
PA4.GPIOParameters=GPIO_PuPd,GPIO_Label
PA4.GPIO_Label=RDYin
PA4.GPIO_PuPd=GPIO_PULLUP
PA4.Signal=GPIO_Input
PA5.Mode=TX_Only_Simplex_Unidirect_Master
PA5.Signal=SPI1_SCK
PA6.GPIOParameters=GPIO_PuPd,GPIO_Label,GPIO_ModeDefaultOutputPP
PA6.GPIO_Label=RDYout
PA6.GPIO_ModeDefaultOutputPP=GPIO_MODE_OUTPUT_OD
PA6.GPIO_PuPd=GPIO_NOPULL
PA6.Signal=GPIO_Output
PA7.Mode=TX_Only_Simplex_Unidirect_Master
PA7.Signal=SPI1_MOSI
PB1.GPIOParameters=GPIO_Speed,PinState,GPIO_PuPd,GPIO_Label,GPIO_ModeDefaultOutputPP
PB1.GPIO_Label=COM1
PB1.GPIO_ModeDefaultOutputPP=GPIO_MODE_OUTPUT_OD
PB1.GPIO_PuPd=GPIO_NOPULL
PB1.GPIO_Speed=GPIO_SPEED_FREQ_LOW
PB1.PinState=GPIO_PIN_SET
PB1.Signal=GPIO_Output
PB8.GPIOParameters=PinState,GPIO_PuPd,GPIO_Label,GPIO_ModeDefaultOutputPP
PB8.GPIO_Label=COM2
PB8.GPIO_ModeDefaultOutputPP=GPIO_MODE_OUTPUT_OD
PB8.GPIO_PuPd=GPIO_NOPULL
PB8.PinState=GPIO_PIN_SET
PB8.Signal=GPIO_Output
PF0-OSC_IN.GPIOParameters=GPIO_Pu
PF0-OSC_IN.GPIO_Pu=GPIO_NOPULL
PF0-OSC_IN.Mode=I2C
PF0-OSC_IN.Signal=I2C1_SDA
PF1-OSC_OUT.GPIOParameters=GPIO_Pu
PF1-OSC_OUT.GPIO_Pu=GPIO_NOPULL
PF1-OSC_OUT.Mode=I2C
PF1-OSC_OUT.Signal=I2C1_SCL
RCC.SYSCLKFreq_VALUE=24000000
RCC.SYSCLKSource=RCC_SYSCLKSOURCE_PLLCLK
board=custom

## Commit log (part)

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2012-04-16 Initial directory structure.
2012-06-06 Initial upload of the Mozc-morse project.
2013-04-19 Initial upload of the Patapata input device firmware. Moving Morse key files to mozc-morse/ directory.
2013-04-19 Addition of a Readme file at the top level directory.
2015-03-25 Migrating wiki contents from Google Code
2015-03-25 Rename ProjectHome.md to README.md
2015-03-31 Fix a typo in README.
2015-03-31 Initial checkin of piropiro version.
2015-04-01 Add "ra" column to the input character list.
2015-04-03 Revise README to remove some redundancy. Add a photo of example device for assembly reference.
2015-06-11 Fixed 2 non-manifold STL data which were not able to 3D print themselves
2015-08-06 Add CONTRIBUTING file.
2015-08-10 Update STL files. - mesh density adjustment to improve precision - re-orientation to facilitate 3D printing - removal of unnecessary faces to prevent non-manifold errors
2016-03-31 Initial upload of the Physical Flick keyboard files.
2016-04-01 Add MCP3208 to the electronic parts list.
2016-04-01 Add some photos of an example device for reference.
2016-04-13 Add file.
2016-04-14 Fixed.
2016-04-22 Keytable update.
2016-04-26 Add some files.
2016-04-28 Add README.md
2017-03-28 Cleaned up the licensing.
2017-03-31 mozc-puchi upload
    mozc-puchi files are uploaded.
2017-03-31 latest readme
    updated and changed UTF-8
2017-03-31 license changed
    fixed
2017-03-31 fixed
    fixed
2017-03-31 back to original
    back to original
2017-03-31 Add puchi-puchi version.
2017-12-15 README.md: Fix typo
2018-03-08 Renamed
2018-03-31 Add nazoru-input in mozc-nazoru/
2018-03-31 Update the path to the schematic
2018-04-02 Update README.rst
    - Explicitly install nazoru-input from PyPi.
    - Remove unnecessary indents
    - apt install for necessary packages (tested on a fresh Debian 9 image on GCE).
2018-04-04 Specify encoding in reading README.rst from setup.py.
2018-04-04 Use directional and temporal features by default.
2018-04-04 Add PyPi badge in README.
2018-06-26 Shorten the wait time.
2018-08-03 Shorten the waiting time until inference
2018-08-03 Add a LED for chassis
2018-08-03 Make it work not on raspberry pi
2018-08-03 Change the brightness
2018-08-03 Add a LED in chassis (#18)
    LED was equipped in the chassis. This patch turns it on.
    SlowLED changes the brightness gradually. wiringpi is used for it to leverage the hardware PWA equipped by Raspberry Pi.
2018-09-11 More consistent demo
2018-09-11 Read ANSI escape codes by KeyboardRecorderFromConsole
2018-09-11 Add DELETE
2018-09-11 Move filterwarnings to the top and surpress FutureWarning too
2018-09-12 Refresh CLI output by input.
2019-03-31 add a newline
2019-03-31 Add mozc-mageru/ for Gboard Spoon Bending Version
2019-04-07 Remove wiringpi from OSX dependency
2019-04-09 Fix dependent module versions
2019-08-03 Add command to enable/disable key output.
    This function is needed for preventing the device from submitting serial
    commands by itself during calibration.
2020-12-02 Upgrade TensorFlow to 1.15.4
2021-09-16 Update TF version
2021-09-30 Add mozc-yunomi for Gboard Yunomi Version.
2021-10-01 Add link to Gboard yunomi version blog post.
2021-10-04 Rename board directories and add mount hole in base-pcb.
2021-10-08 Add silk-screen for USB connector pin assignment.
2021-11-15 Add yunomi base board for promicro.
2021-12-08 Update firmware to support promicro.
2021-12-10 Fix bug.
2021-12-12 Fix key mapping for osakana.
2021-12-16 Add README for Pro Micro
2022-06-06 Remove Kicad cache files
2022-06-06 TensorFlow version up
2022-10-01 Add mozc-bar for Gboard bar version.
2022-10-08 mozc-bar: Remove PCB shape from type-D case shape data.
    The shape of the PCB was merged into the STL data for type-D case by
    mistake.
2022-10-08 mozc-bar: Remove PCB shape from type-D shape data.
    The shape of the PCB was included in the case shape data for type-D case
    by mistake.
2023-03-23 This is a bug bounty test. Please ignore.. (rlciri)
2023-03-25 Update README.md
    PCB及びcaseの準備数がキーマップング画像とファームウェアと差異があったため修正
2023-03-27 [Mozc-bar] Fix length of the frame. (See #46 for details)
2023-04-09 Bug bounty test - please ignore.... (sbqxit)
2023-10-01 Add mozc-caps.
2023-10-09 Update mozc-caps.ino
    Implement the commit() function within the Compositor class. This function is designed to finalize the Japanese composition process by simulating the pressing of the Enter key, effectively submitting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
2024-09-30 Add mozc double sided version.
    Reviewed-by: Eliot Courtney <edcourtney@google.com>
2024-10-01 Fix links for flap and yunomi.
2024-10-01 Fix release date for puchi and nazoru
2024-10-01 Fix release date for magichand.
2024-10-01 Update mozc-doublesided/README.md to avoid unsupported syntax
2024-10-03 Add command to enable/disable key output. (#29)
    This function is needed for preventing the device from submitting serial
    commands by itself during calibration.
2024-10-04 Specify required Python versions to align with TF2.12
2024-12-21 Update README.md
    Fix spelling mistake.
2025-10-03 Fix link text for Gboard Dial Version

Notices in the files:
mozc-doublesided/README.md:
See [LICENSE](../LICENSE) file in this directory.
